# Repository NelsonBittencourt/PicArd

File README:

These are the KiCad files for a Nano version of the programer

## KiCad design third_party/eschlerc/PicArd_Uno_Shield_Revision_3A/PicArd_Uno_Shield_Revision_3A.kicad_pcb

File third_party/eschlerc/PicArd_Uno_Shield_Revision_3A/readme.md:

## Third-party Contribution Folder

User: [eschlerc](https://github.com/eschlerc)

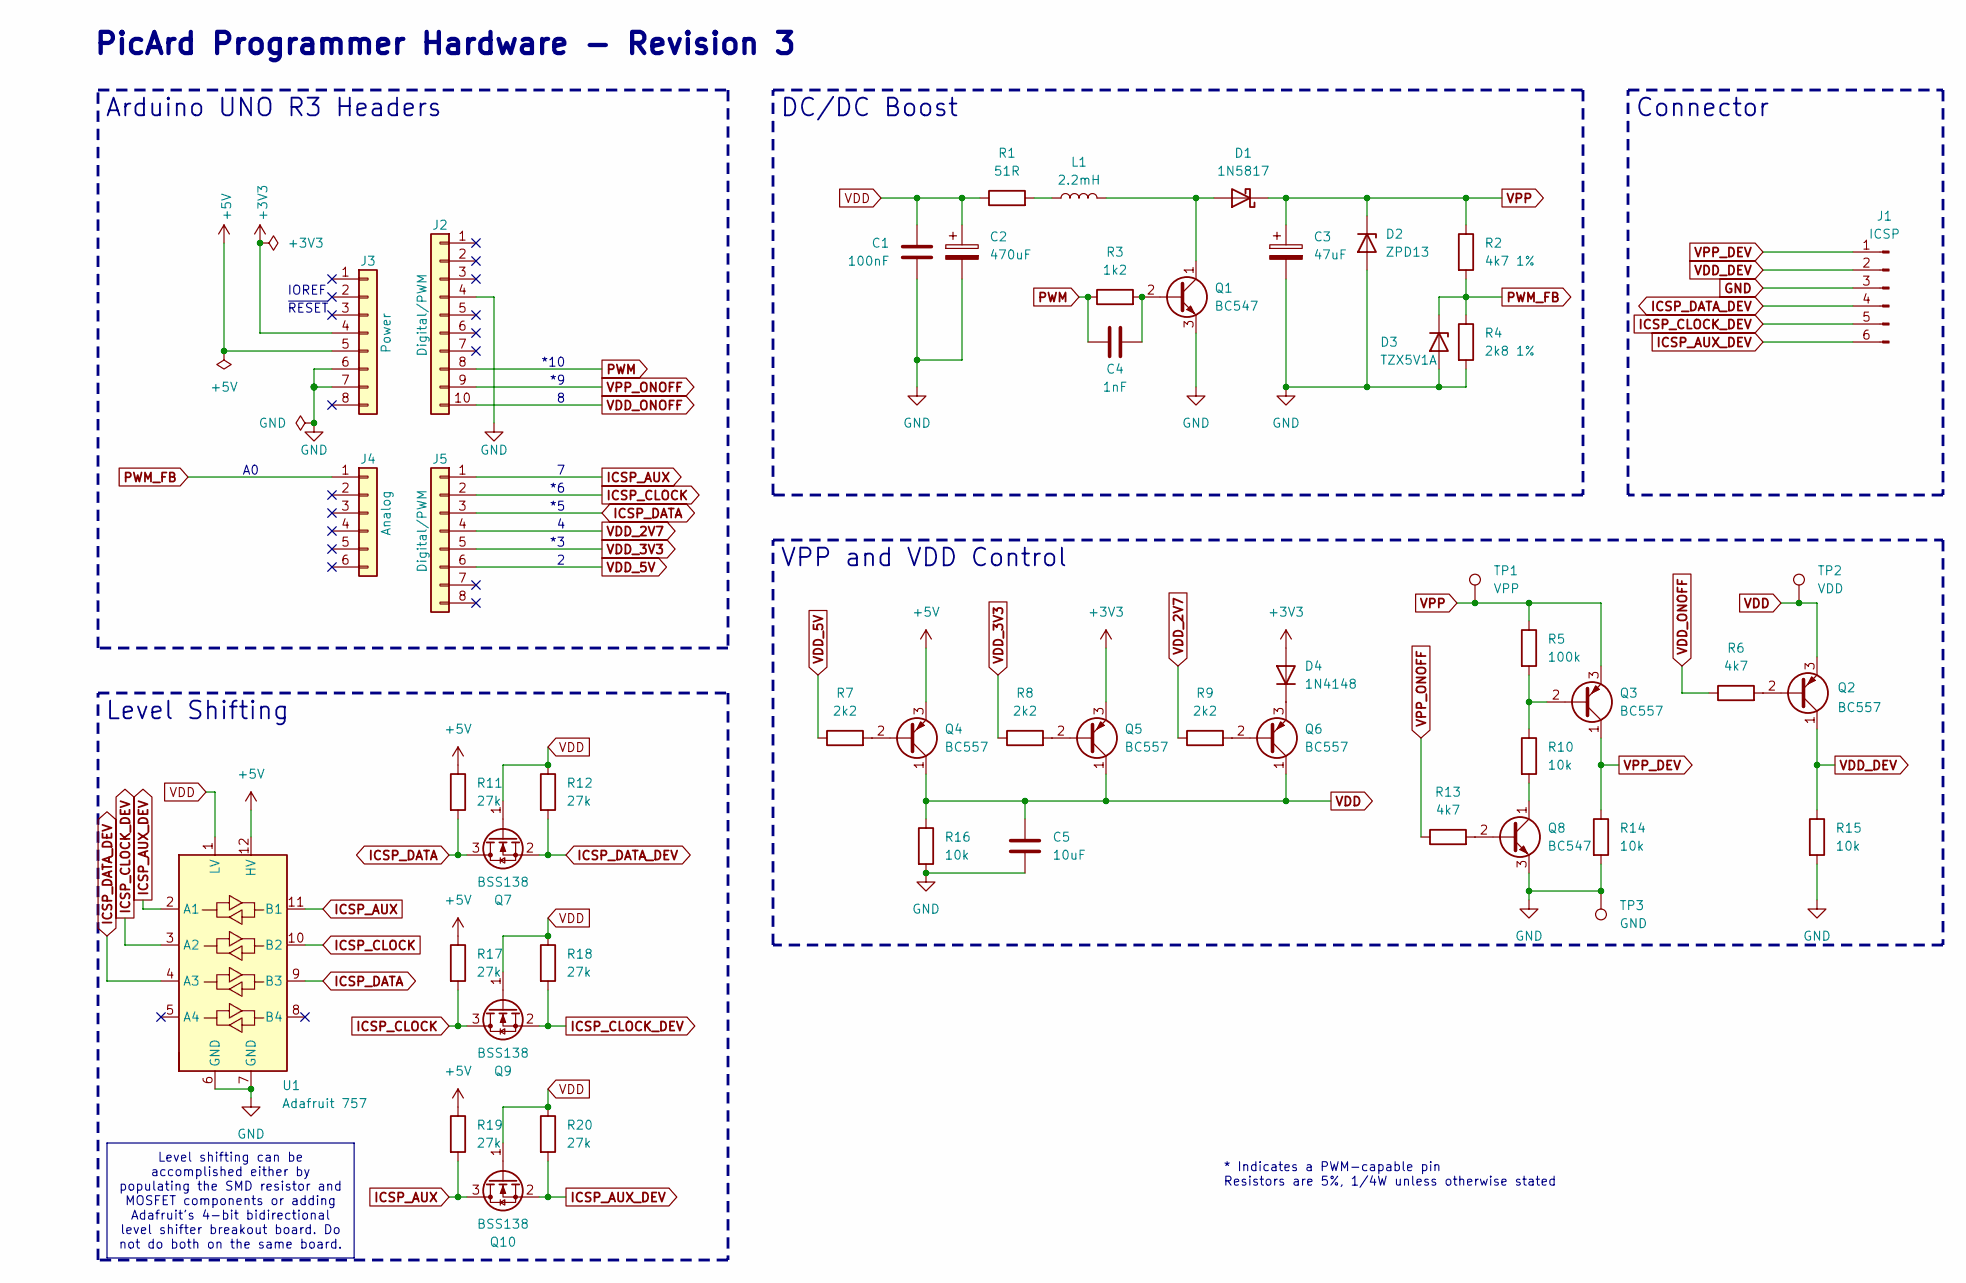
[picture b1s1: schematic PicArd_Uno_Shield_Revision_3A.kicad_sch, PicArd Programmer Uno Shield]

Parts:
C1: 100nF; C_Axial_L5.1mm_D3.1mm_P7.50mm_Horizontal
C2: 470uF; CP_Radial_D8.0mm_P3.50mm
C3: 47uF; CP_Radial_D10.0mm_P5.00mm
C4: 1nF; C_Disc_D4.7mm_W2.5mm_P5.00mm
C5: 10uF; C_Disc_D5.1mm_W3.2mm_P5.00mm
D1: 1N5817; D_DO-41_SOD81_P7.62mm_Horizontal
D2: ZPD13; D_DO-35_SOD27_P7.62mm_Horizontal
D3: TZX5V1A; D_DO-35_SOD27_P7.62mm_Horizontal
D4: 1N4148; D_DO-35_SOD27_P7.62mm_Horizontal
J1: ICSP; PinHeader_1x06_P2.54mm_Vertical
J2: Digital/PWM; PinSocket_1x10_P2.54mm_Vertical
J3: Power; PinSocket_1x08_P2.54mm_Vertical
J4: Analog; PinSocket_1x06_P2.54mm_Vertical
J5: Digital/PWM; PinSocket_1x08_P2.54mm_Vertical
L1: 2.2mH; L_Radial_D7.0mm_P3.00mm
Q1, Q8: BC547; TO-92_Inline_Wide
Q2, Q3, Q4, Q5, Q6: BC557; TO-92_Inline_Wide
Q7, Q9, Q10: BSS138; SOT-23
R1: 51R; R_Axial_DIN0309_L9.0mm_D3.2mm_P12.70mm_Horizontal
R2: 4k7 1%; R_Axial_DIN0207_L6.3mm_D2.5mm_P7.62mm_Horizontal
R3: 1k2; R_Axial_DIN0207_L6.3mm_D2.5mm_P7.62mm_Horizontal
R4: 2k8 1%; R_Axial_DIN0207_L6.3mm_D2.5mm_P7.62mm_Horizontal
R5: 100k; R_Axial_DIN0207_L6.3mm_D2.5mm_P7.62mm_Horizontal
R6, R13: 4k7; R_Axial_DIN0207_L6.3mm_D2.5mm_P7.62mm_Horizontal
R7, R8, R9: 2k2; R_Axial_DIN0207_L6.3mm_D2.5mm_P7.62mm_Horizontal
R10, R14, R15, R16: 10k; R_Axial_DIN0207_L6.3mm_D2.5mm_P7.62mm_Horizontal
R11, R12, R17, R18, R19, R20: 27k; R_0805_2012Metric
TP1: VPP; TestPoint_Pad_D1.5mm
TP2: VDD; TestPoint_Pad_D1.5mm
TP3: GND; TestPoint_Pad_D1.5mm
U1: Adafruit 757; DIP-12_W10.16mm

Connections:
+3V3: D4.2 (A), J3.4, Q5.3 (E)
+5V: J3.5, Q4.3 (E), R11.1, R17.1, R19.1, U1.12 (HV)
GND: C1.2, C2.2, C3.2, C5.2, D2.2 (A), D3.2 (A), J1.3, J2.4, J3.6, J3.7, Q1.3 (E), Q8.3 (E), R4.2, R14.2, R15.2, R16.2, TP3.1 (1_1), U1.6 (GND), U1.7 (GND)
ICSP_AUX: J5.1, Q10.3 (D), R19.2, U1.11 (B1)
ICSP_AUX_DEV: J1.6, Q10.2 (S), R20.2, U1.2 (A1)
ICSP_CLOCK: J5.2, Q9.3 (D), R17.2, U1.10 (B2)
ICSP_CLOCK_DEV: J1.5, Q9.2 (S), R18.2, U1.3 (A2)
ICSP_DATA: J5.3, Q7.3 (D), R11.2, U1.9 (B3)
ICSP_DATA_DEV: J1.4, Q7.2 (S), R12.2, U1.4 (A3)
unnamed: D1.2 (A), L1.2, Q1.1 (C)
unnamed: D4.1 (K), Q6.3 (E)
unnamed: L1.1, R1.2
unnamed: C4.2, Q1.2 (B), R3.2
unnamed: Q2.2 (B), R6.2
unnamed: Q3.2 (B), R5.2, R10.1
unnamed: Q4.2 (B), R7.2
unnamed: Q5.2 (B), R8.2
unnamed: Q6.2 (B), R9.2
unnamed: Q8.2 (B), R13.2
unnamed: Q8.1 (C), R10.2
PWM: C4.1, J2.8, R3.1
PWM_FB: D3.1 (K), J4.1 (Pin_1_1), R2.2, R4.1
VDD: C1.1, C2.1, C5.1, Q2.3 (E), Q4.1 (C), Q5.1 (C), Q6.1 (C), Q7.1 (G), Q9.1 (G), Q10.1 (G), R1.1, R12.1, R16.1, R18.1, R20.1, TP2.1 (1_1), U1.1 (LV)
VDD_2V7: J5.4, R9.1
VDD_3V3: J5.5, R8.1
VDD_5V: J5.6, R7.1
VDD_DEV: J1.2, Q2.1 (C), R15.1
VDD_ONOFF: J2.10, R6.1
VPP: C3.1, D1.1 (K), D2.1 (K), Q3.3 (E), R2.1, R5.1, TP1.1 (1_1)
VPP_DEV: J1.1, Q3.1 (C), R14.1
VPP_ONOFF: J2.9, R13.1

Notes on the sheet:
PicArd Programmer Hardware - Revision 3
~{RESET}
*10
IOREF
* Indicates a PWM-capable pin Resistors are 5%, 1/4W unless otherwise stated
Level Shifting
DC/DC Boost
Connector
VPP and VDD Control
Arduino UNO R3 Headers
Level shifting can be accomplished either by populating the SMD resistor and MOSFET components or adding Adafruit's 4-bit bidirectional level shifter breakout board. Do not do both on the same board.

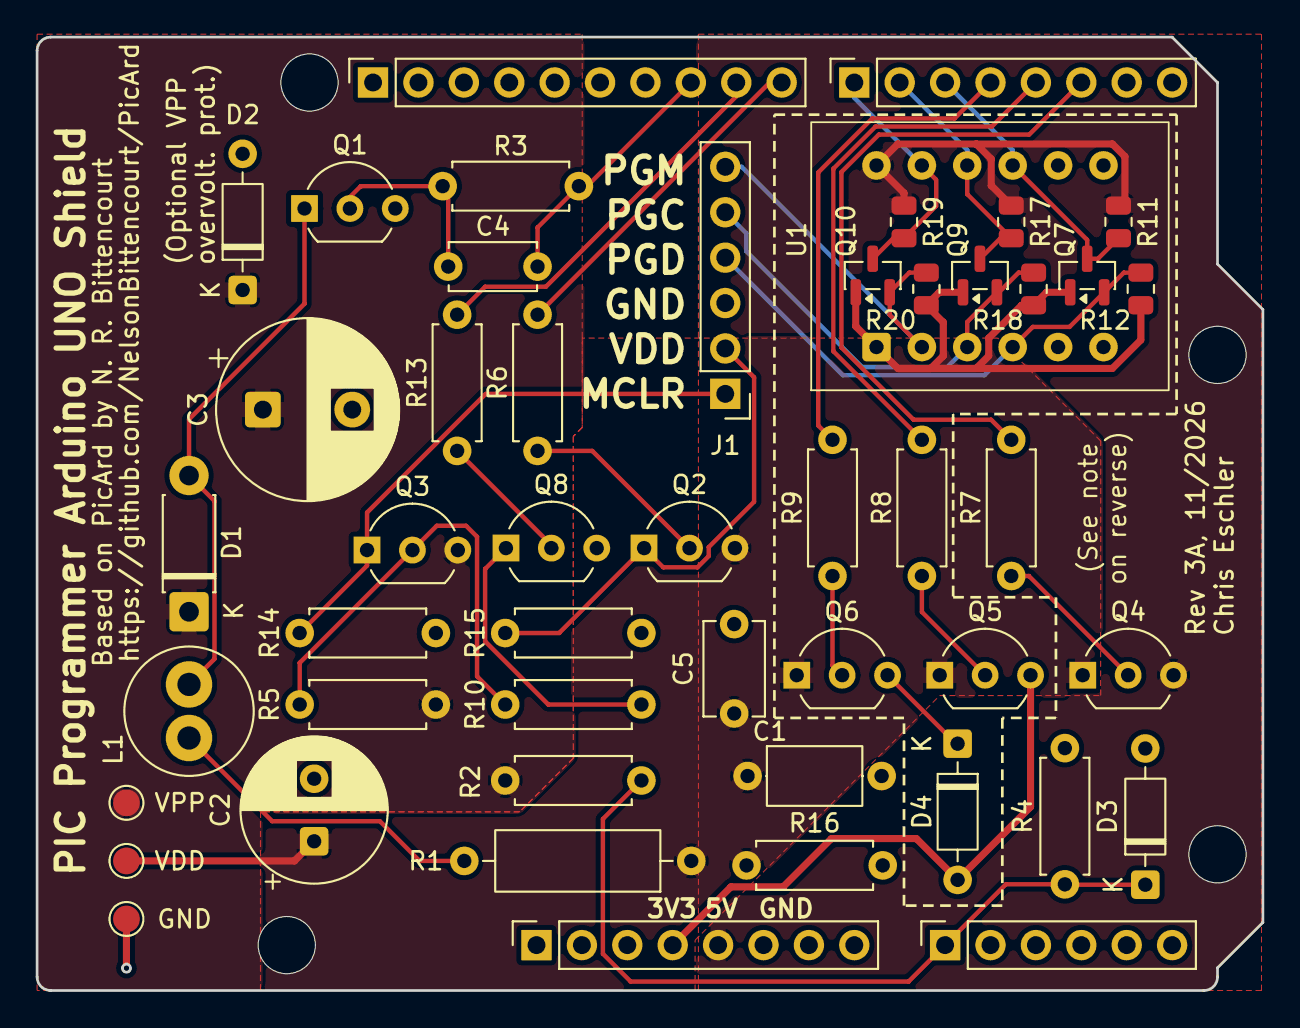
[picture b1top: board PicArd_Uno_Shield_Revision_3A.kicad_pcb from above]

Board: 2 copper layers, 68.6 x 53.3 mm, 53 parts (0 on the bottom side), 31 nets.

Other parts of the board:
MH1, MH2, MH3, MH4: MountingHole_3.2mm

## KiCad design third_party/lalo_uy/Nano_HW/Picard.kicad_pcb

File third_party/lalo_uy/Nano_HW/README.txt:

These are the KICad files of a Nano version of the programer

@NelsonBittencourt note: 
There is an error in this PicArd Nano version. The Nano board 5V pin is an input pin, not an output. Thus, when using USB to power the board, the 5V pin will provide (5V-{diode voltage drop}). To correct this, connect the PicArd 5V pin directly to USB 5V rail.

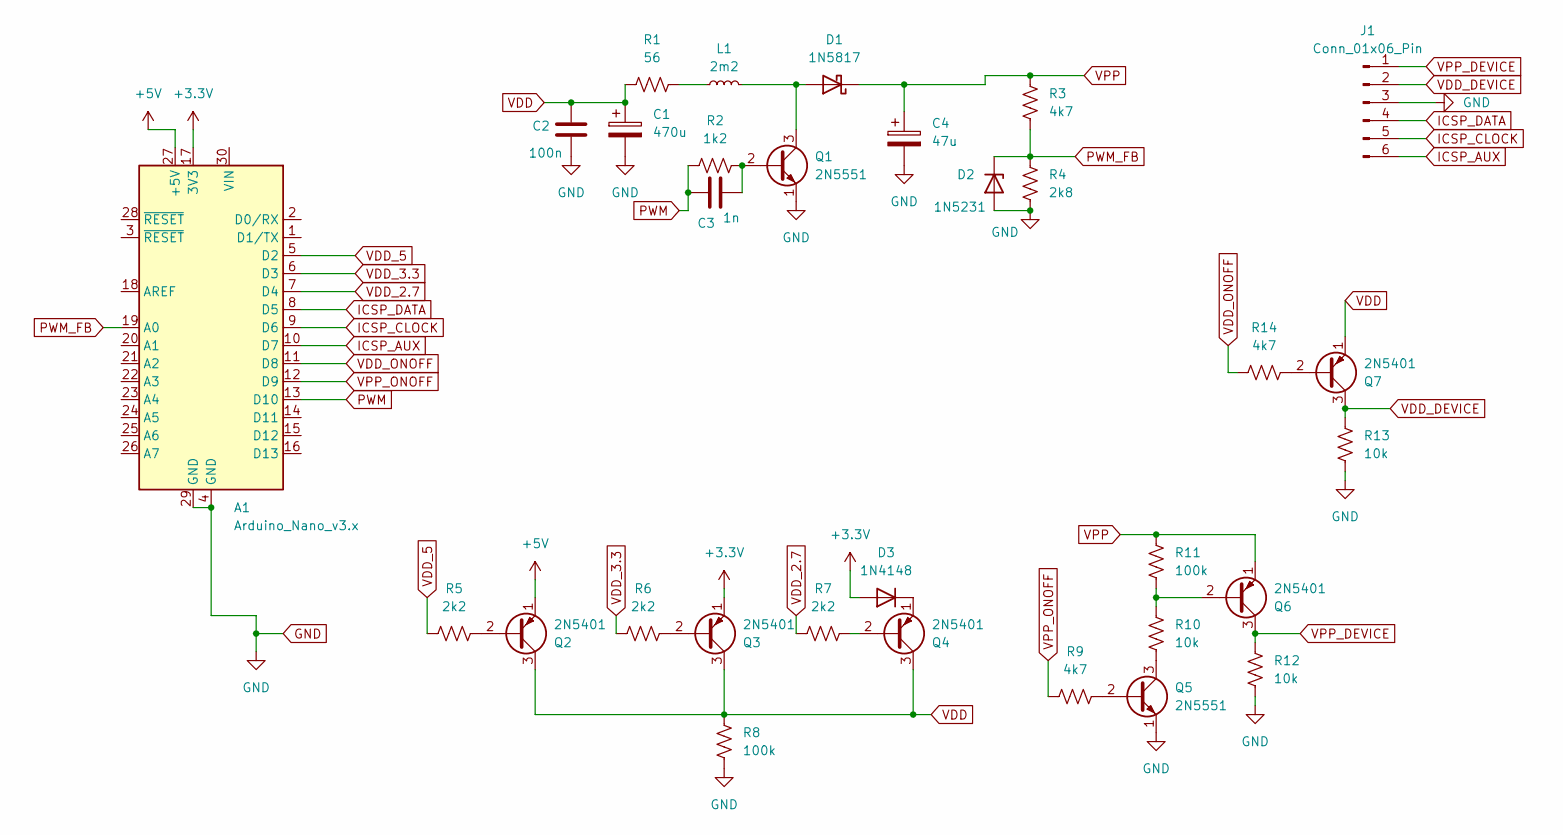
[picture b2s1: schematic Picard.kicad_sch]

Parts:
A1: Arduino_Nano_v3.x; Arduino_Nano
C1: 470u; CP_Radial_D10.0mm_P5.00mm
C2: 100n; C_Axial_L3.8mm_D2.6mm_P7.50mm_Horizontal
C3: 1n; C_Axial_L3.8mm_D2.6mm_P7.50mm_Horizontal
C4: 47u; CP_Radial_D5.0mm_P2.50mm
D1: 1N5817; D_DO-41_SOD81_P10.16mm_Horizontal
D2: 1N5231; D_DO-201_P15.24mm_Horizontal
D3: 1N4148; D_DO-35_SOD27_P7.62mm_Horizontal
J1: Conn_01x06_Pin; PinHeader_1x06_P2.54mm_Vertical
L1: 2m2; L_Axial_L5.0mm_D3.6mm_P10.00mm_Horizontal_Murata_BL01RN1A2A2
Q1, Q5: 2N5551; TO-92_Inline_Wide
Q2, Q3, Q4, Q6, Q7: 2N5401; TO-92_Inline_Wide
R1: 56; R_Axial_DIN0207_L6.3mm_D2.5mm_P10.16mm_Horizontal
R2: 1k2; R_Axial_DIN0207_L6.3mm_D2.5mm_P10.16mm_Horizontal
R3, R9, R14: 4k7; R_Axial_DIN0207_L6.3mm_D2.5mm_P10.16mm_Horizontal
R4: 2k8; R_Axial_DIN0207_L6.3mm_D2.5mm_P10.16mm_Horizontal
R5, R6, R7: 2k2; R_Axial_DIN0207_L6.3mm_D2.5mm_P10.16mm_Horizontal
R8, R11: 100k; R_Axial_DIN0207_L6.3mm_D2.5mm_P10.16mm_Horizontal
R10, R12, R13: 10k; R_Axial_DIN0207_L6.3mm_D2.5mm_P10.16mm_Horizontal

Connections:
+3.3V: A1.17 (3V3), D3.2 (A), Q3.1 (E)
+5V: A1.27 (+5V), Q2.1 (E)
GND: A1.4 (GND), A1.29 (GND), C1.2, C2.2, C4.2, D2.2 (A), J1.3, Q1.1 (E), Q5.1 (E), R4.1, R8.1, R12.1, R13.1
ICSP_AUX: A1.10 (D7), J1.6
ICSP_CLOCK: A1.9 (D6), J1.5
ICSP_DATA: A1.8 (D5), J1.4
unnamed: D1.2 (A), L1.2, Q1.3 (C)
unnamed: D3.1 (K), Q4.1 (E)
unnamed: L1.1, R1.2
unnamed: C3.2, Q1.2 (B), R2.2
unnamed: Q2.2 (B), R5.2
unnamed: Q3.2 (B), R6.2
unnamed: Q4.2 (B), R7.2
unnamed: Q5.2 (B), R9.2
unnamed: Q5.3 (C), R10.1
unnamed: Q6.2 (B), R10.2, R11.1
unnamed: Q7.2 (B), R14.2
PWM: A1.13 (D10), C3.1, R2.1
PWM_FB: A1.19 (A0), D2.1 (K), R3.1, R4.2
VDD: C1.1, C2.1, Q2.3 (C), Q3.3 (C), Q4.3 (C), Q7.1 (E), R1.1, R8.2
VDD_2.7: A1.7 (D4), R7.1
VDD_3.3: A1.6 (D3), R6.1
VDD_5: A1.5 (D2), R5.1
VDD_DEVICE: J1.2, Q7.3 (C), R13.2
VDD_ONOFF: A1.11 (D8), R14.1
VPP: C4.1, D1.1 (K), Q6.1 (E), R3.2, R11.2
VPP_DEVICE: J1.1, Q6.3 (C), R12.2
VPP_ONOFF: A1.12 (D9), R9.1

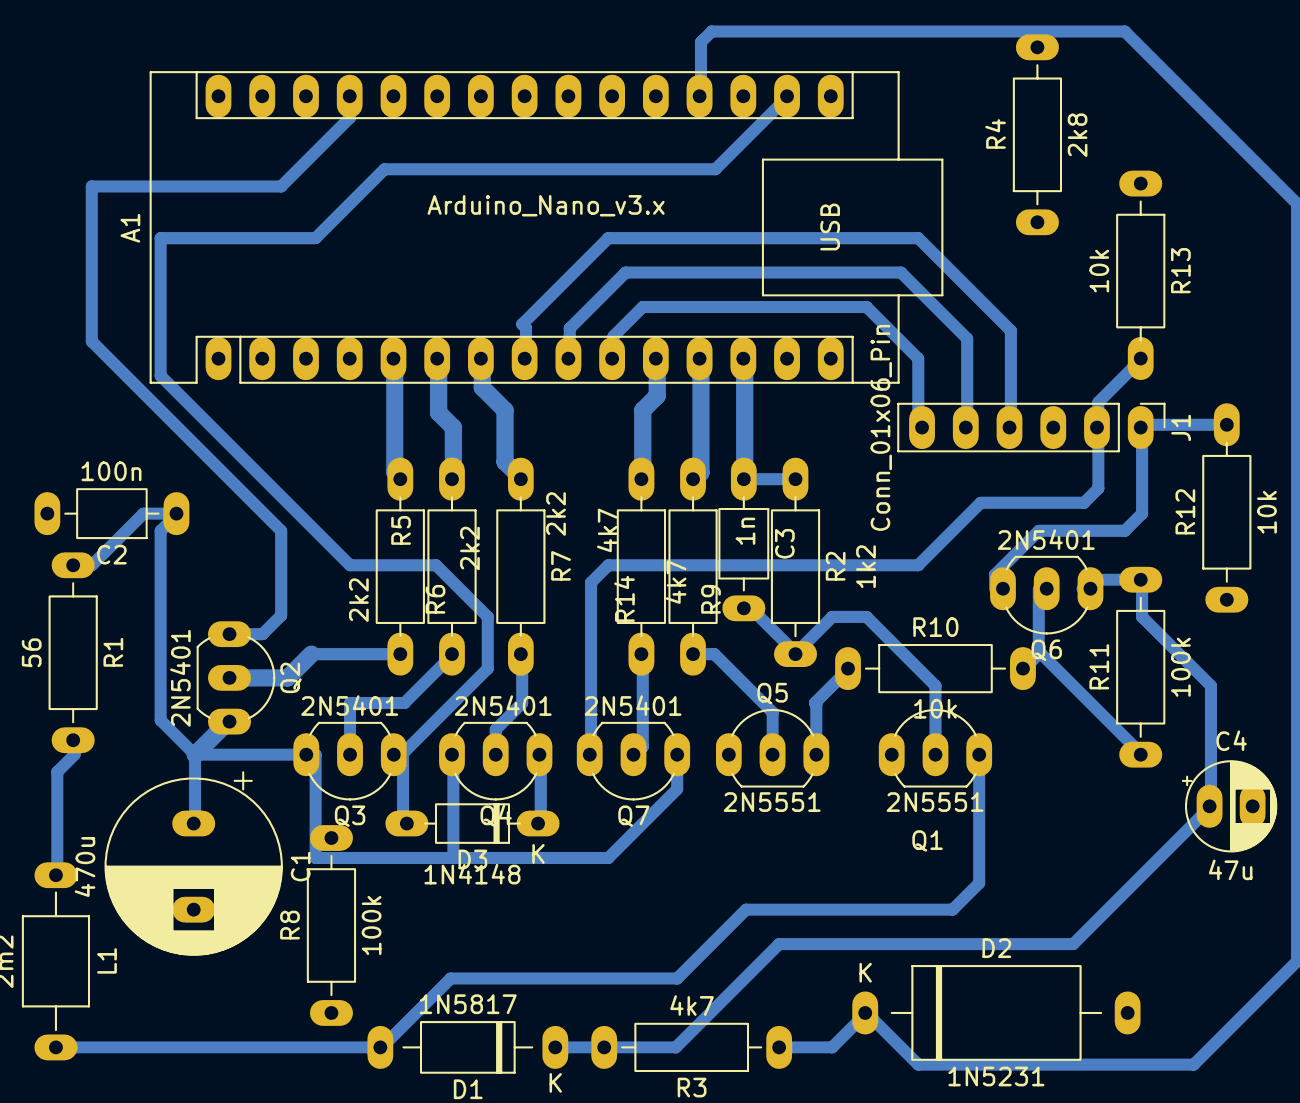
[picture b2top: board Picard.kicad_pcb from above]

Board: 2 copper layers, 31 parts (0 on the bottom side), 28 nets.

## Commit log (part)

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2024-05-20 Update LICENSE
2025-11-14 version 0.41
2025-11-14 Create docs
2025-11-14 Create test
2025-11-14 Create null
2026-02-19 Update for PicArd GUI version
2026-02-19 Linux version warning about USB access
2026-02-23 Tmp images to test
2026-02-23 Arduino Uno Shield - Gerber Files
2026-02-23 Added Arduino Uno Shield Gerber Files
2026-04-09 v042
    Changes:
    -PWM output pin from D11 to D10 and
    -Footprints (R2, R10 e T4).
2026-04-09 v042
    Changes:
    -PWM frequency (from 62.5kHz to 125kHz);
    -New PID parameters;
    -Anti-windup;
    -Feed-back voltage new scan time and
    -Minor changes for increase code performance.
2026-04-09 0.42
